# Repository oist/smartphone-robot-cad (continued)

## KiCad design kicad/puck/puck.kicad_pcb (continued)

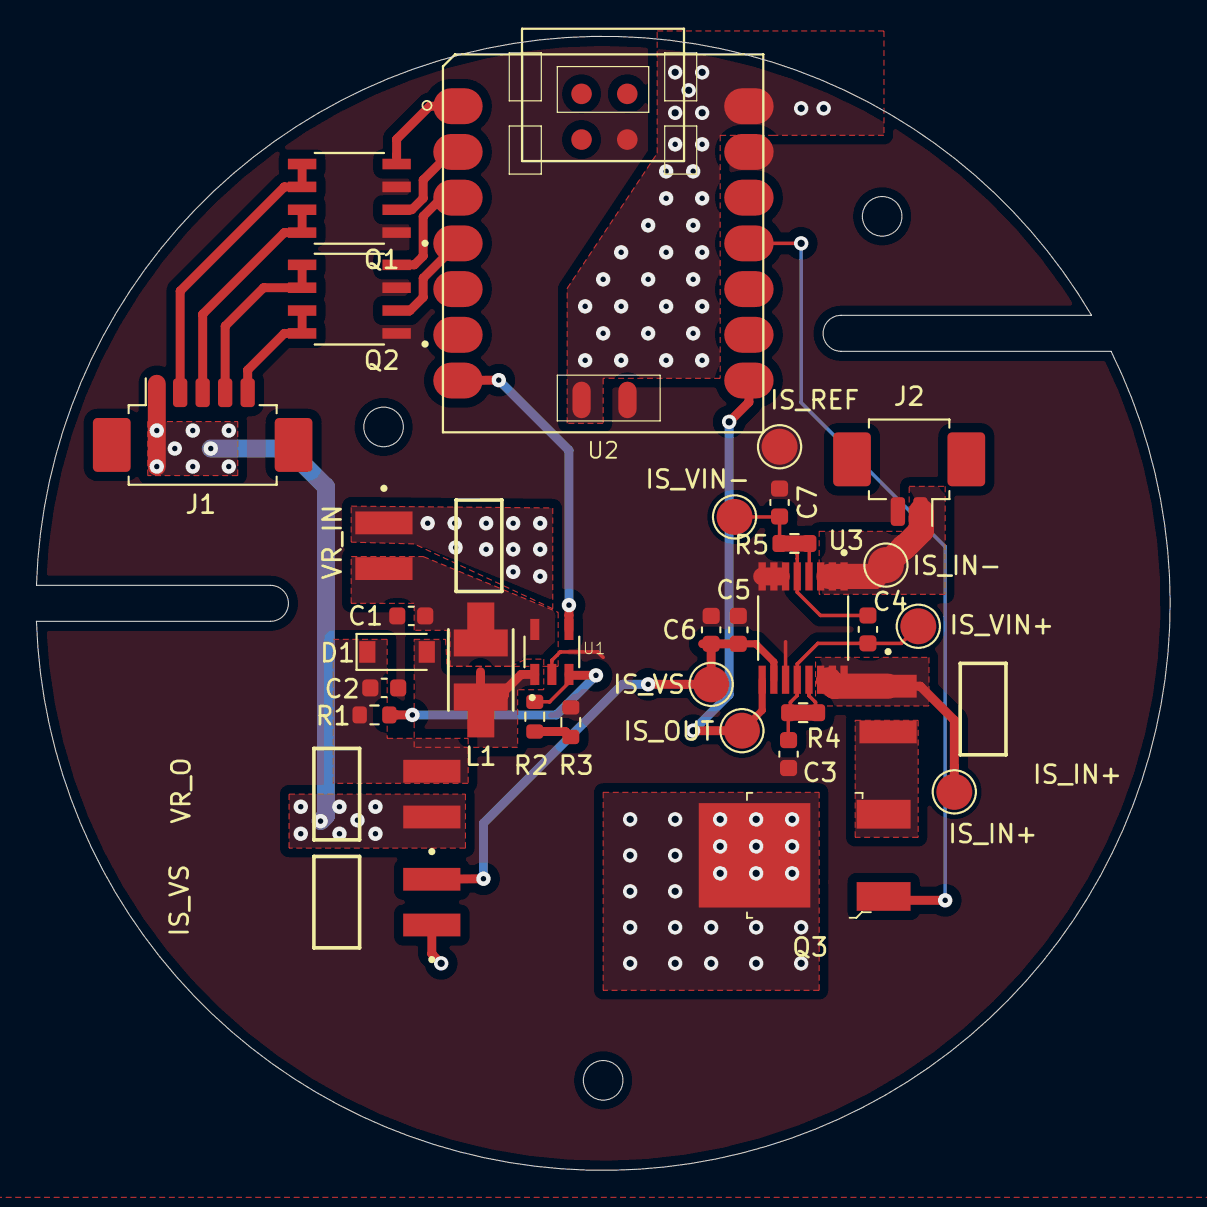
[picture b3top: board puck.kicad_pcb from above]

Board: 2 copper layers, 63.0 x 63.0 mm, 33 parts (0 on the bottom side), 27 nets.

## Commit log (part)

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2023-06-06 Updating working dir for config
2023-06-06 Adding gitignore for config
2023-06-07 Rebased footprints module onto current master
2023-07-19 Adding separable pin headers symbols for longer pin header
2023-07-19 Add button for boot select like on PICO to allow drag/drop programming
2023-07-19 Adding TL3305AF260QG
2023-07-19 Add current breaks between each section of hardware.
2023-07-19 Made R66 DNP
2023-07-19 Added set resistor for LDO and changed size to 0603 for LDO output capacitor as recommended by datasheet Output Capacitor Selection
2023-07-19 custom_transistors:ON_Semiconductor-568AL-10_2013-O-MFG footprint 3d model dot to correct corner
2023-07-19 Updated voltage translation mosfets to lower V_th mosfets
2023-07-19 Adding JST_-_B6B-ZR-SM4-TF
2023-07-19 Hold bufferin rp2040sheet to vio during startup
2023-07-19 Added RC2 voltage translator
2023-07-19 Hide all test point values keep ref
2023-07-19 Adding 7.0 config files
2023-07-25 Removing firmware-specific submodules from pcb branch
2023-07-25 Adding wireless coil jst header
2023-07-26 Updating kicad_common.json to correct directories
2023-07-26 Adding switch to connect d+/- from both USB from Pc to pi
2023-07-26 Adding motor and wheels to custom_connectors.pretty/CONN_B6B-ZR-SM4-TF_JST.kicad_mod
2023-07-26 Flipping battery to other side of board
2023-07-27 Eleminated 5V rail and corrected a few mistakes in SIMO config
2023-07-30 Updating reference after seeing Archive3DModels fail
2023-07-31 Export 3D models to local project
2023-07-31 Fixed floating zone supposed to be GND
2023-07-31 Added removed Package_X1SON:TPD1E05U06DPYR
2023-07-31 updated all footprint fields in schematic symbols with local robot ones
2023-07-31 Exported all schematic symbols to local robot and refer to them in all symbols
2023-07-31 Adding Switch_R_SMD_3pin symbol
2023-07-31 removed i2c switch for external master. Not needed due to not using custom scripts on the Max77958 in favor of mcu control via firmware
2023-07-31 Adding JS202011JCQN to project in place of other switch
2023-07-31 Swapping out SW4_PTS815 SJM 250 SMTR LFS_CNK for prevvious tactile switch on rp2040
2023-07-31 Adding XTAL_ECS-120-8-36-CKM-TR3 in place of previous crystal
2023-08-01 Replaced all test points with SMD parts where possible
2023-08-01 Moving SWCLK and SWD to pin header on rp2040 UART
2023-08-01 finished grouping paired 0ohm resistors
2023-08-01 Adding power flags to side of 0ohm resistors for electrical checks
2023-08-01 Ignoring some warnings about GND naming duplications. Electrical Rules Checker clear.
2023-08-01 Adding THT leads for rocker switch and 2 ohm resistors to implement it if needed
2023-08-02 Adding B12H1UYG-20D000134U1930 LED
2023-08-02 Swapped all LEDS out for board edge ones
2023-08-02 Replacing LEDs with side mounted ones, and added an LED driver for the two that don't have a driver
2023-08-04 Adding robot lib to favorites
2023-08-04 adding SW_SPST symbol to robot lib
2023-08-04 Adding TE_1-1123723-2 to lib
2023-08-04 Exported step file for motor
2023-08-04 Added similar JST connector
2023-08-04 init commit of micromotor
2023-08-04 Added 90mm wheels step and to assembly
2023-08-04 Added 40mm wheels step and to assembly
2023-08-04 Rearanged tree for motor
2023-08-04 Made PCB assembly and added to Robot
2023-08-04 Added initial sketch for body enclosure
2023-08-04 Aligned wheels and motor and phone to get a sense of spacing.
2023-08-04 Adding init blender file
2023-08-05 Adding plug to motor cable 3d model
2023-08-05 Adding pixel3a mount
2023-08-05 Adding prl config file to gitignore
2023-08-05 Adding header models to local as well
2023-08-05 Updated phone mounting sleeve and position
2023-08-05 Locking positions of phone, motors, and battery
2023-08-05 changed colors of pixel3a models
2023-08-06 Moving battery back but with enough space for mounting holes
2023-08-06 wip pixel mount
2023-08-06 wip 3d models
2023-08-07 wip models
2023-08-07 Adding load switch to battery protection circuit
2023-08-07 Moving molex and wheel connectors around
2023-08-07 Adding robot.pretty/MountingHole_2.2mm_M2.kicad_mod
2023-08-07 Increased clearance on mounting holes
2023-08-07 Removing duplicate headers
2023-08-08 Updating battery holder footprint to include gaps in courtyard
2023-08-08 Removing no longer relevant text comment about alternative headers
2023-08-08 changing UART header to 2.54mm header and moving bulk capacitance after load switch.
2023-08-08 reset the offset of qfn
2023-08-08 adding a couple more local 3d packages
2023-08-09 Removing changes to kicad_pro made by Kadir on accident
2023-08-09 Removing a bunch of unneccesary symbol properties
2023-08-09 Adding pin numbers for connector to remove PCB error
2023-08-09 added erc exclusions
2023-08-09 Updating power flag to local symbol
2023-08-10 updating all footprints from lib. Rotated a bunch of pads from 270 to 90 and so forth. Looks like might have come from when flipped all parts to other side of board?
2023-08-10 fixed hovering AP33771DKZ13 model
2023-08-10 Updated battery model offset to match library
2023-08-10 updating global paths to 3d models to project relative ones for usb for phone and motor headers
2023-08-10 placed remaining components
2023-08-10 Adding back in exclusions
2023-08-10 Thinned out silkscreen lines so not on top of pad for USB4120-03-C_REVA
2023-08-11 Updated errors in SN74AHC125RGYR footprint including non-mask defined pads
2023-08-11 Added GND vias to isolated zone and removed all zones < 20mm^2
2023-08-11 Adding courtyard to TVS0500DRVR
2023-08-11 moved tp32 above tp31
2023-08-11 fixed c37-c17 gnd connection error
2023-08-11 move tp21 to more accessible place
2023-08-11 Rotated a few smd test points and moved LEDs closer to board edge
2023-08-11 adding a bunch of thermal reliefs
2023-08-11 Adding a few more warnings for DRC
2023-08-11 Removing some unknown pcb properties
2023-08-11 Updating courtyard on battery. 3d model profile was wrong
2023-08-13 Added all netties and net classes for 3A traces to schematic and updated PCB, but haven' t routed anything yet
2023-08-13 Adding all power_1A net classes and net ties
2023-08-13 Updating symbol fields for BOM completion.
2023-08-13 fixing a few more BOM related issues
2023-08-14 placed netties
2023-08-14 increased trace width btw R73-J4
2023-08-14 fixing Charger.kicad_sch net tie needs on STAT LED and EXTSM also needed to be a signal trace
2023-08-14 Changed 2A net tie to 0.3mm trace tie
2023-08-14 Updating netties to not include polygon
2023-08-14 Changed TP from 5004 to emtpy THT for potential switch later.
2023-08-14 fixed drc errors for TP12
2023-08-14 DRC fixes for R42 net tie errors
2023-08-14 fixing DRC errors associated with SYS in for USB-PD-PhonePC sheet
2023-08-14 fixing net tie issue with VBUS_Phone_PS and nearby nets
2023-08-14 fixing poorly routed GPIO5 on max77958
2023-08-15 Ignoring one more DNP cap warning
2023-08-15 Removed some unconnected tracks
2023-08-15 Fixed scope in rules for inner layers
2023-08-15 Removing old netclass patterns
2023-08-15 Added custom rules to exclude BGA/WLP trace thickness check
2023-08-15 Updating rules to include U16 and U17 for thin traces
2023-08-15 moved test points into battery holder courtyard
2023-08-15 BOM exclusions for net ties and n/a part test points
2023-08-15 BOM value fixes
2023-08-15 Adding robot to pinned symbol libs
2023-08-15 Updating bom.py and robot.xml
2023-08-15 fixed up zone on OUT_P1
2023-08-15 fixed up batt zone
2023-08-15 Updating wireless charger to 3A net class and added zone
2023-08-16 fixing a few more zone related DRC errors
2023-08-16 Adding two more net labels to diff pair signals
2023-08-17 reviewed and made small changes usb data lines
2023-08-17 Adding C_1206_3216Metric_AlPoly_Combo
2023-08-17 Updating footprint for IC_DRV8830DRCR to include vias
2023-08-18 Adding optimal track width for 2A net class
2023-08-18 Major revision moving motor drivers closer to motor headers
2023-08-18 Fixing some more minor DRC errors
2023-08-18 Removing islands from GND zone
2023-08-18 Resolving all DRC and ERC errors/warnings
2023-08-18 Added wireless recevier separate from header
2023-08-18 Adding external switch to BOM
2023-08-18 Adding wheels to sch for BOM
2023-08-18 gerbers submitted to NextPCB
2023-08-21 Updating reference to 1206 cap 3d package to relative path
2023-08-21 Placing origin
2023-08-21 Updating part number for 0805 100uF caps
2023-08-21 updaintg bom.py to include stock for DNP parts
2023-08-22 Adding STWLC38JRM to libs
2023-08-23 wireless receiver schematic finished (other than BOM)
2023-08-23 Updating all wireless passives to required part numbers. Still missing less restrictive ones
2023-08-23 Updating PCB with new footprints
2023-08-23 Updated 100uF caps to 1206 footprint to allow for 6.3V ratings
2023-08-23 First attempt to organize wireless caps
2023-08-23 Updating RMCF0603FT649K to RC0402FR-07649KL
2023-08-23 Adding passive footprint bom generator
2023-08-25 fixed two wrong product foorprint mismatches
2023-08-25 Updating tht mounting holes for coil as not in BOM
2023-08-25 Updated power path from VBus_Ext to top and bottom layers and thicker zone.
2023-08-25 Updating production files
2023-08-28 Updating part number to MAX77857BEWB+
2023-08-28 Updating bom with updated part numbers and stock qty
2023-09-05 updating DRV8830DRCR footprint
2023-09-05 Replacing wrong part number for USB4151-GF-C
2023-09-05 Updating fab files after changes requested from NextPCB
2023-09-13 Adding overlap on nettie footprint as per NextPCB request
2023-09-15 Initial robot body design sent to Ken-san
2023-09-28 Increased size of vias under USB
2023-09-28 Updating gerbers
2023-09-28 Adding type field to all parts for pcbway
2023-09-29 Updated via-in-pad requirements
2023-10-02 Updating gerbers based on 16 quotes
2023-10-03 Moving copper 0.21mm from edge cuts as per recommendation
2023-10-05 Updating full partnumber for powermux
2023-10-05 Replacing YJL3416A with AS2312
2023-10-05 Changing mask to green since jlcpcb charged 0 less for it
2023-10-23 Updating led footprints to indicate diode orientation
2023-10-25 Changing kicad_common.json to gitSSD dir
2023-10-25 Hiding DNP R10 3d model
2023-10-25 Hiding DNP R80 3d model
2023-10-25 Hiding DNP R91 3d model
2023-10-25 Updating paths to 3d models for C109 and C127
2023-10-25 Hiding DNP models for C74, C89, C86, C90
2023-10-25 Hiding DNP models for R13
2023-10-25 Made visible 3d model for C125
2023-11-20 deeper cavity for the pins, and a larger space for the wireless coil
2023-11-22 Updating top cover to include hole for button
2024-01-17 Adding button_hole test and parts
2024-01-31 Adding tests for counter_sunk holes
2024-02-05 Updating size of shaft adapter after initial batch print failed
2024-05-14 Importing 3d cad media from meta project repo
2024-07-10 Removing outdated Tina electrical cad designs
2024-07-10 Removing outdated pspice files
2024-07-10 Removed all outdated files and renamed some to be more descriptive
2024-07-11 Removed a duplicate cad file
2024-07-15 changing dir names for body and pcb
2024-07-23 Reduced width to minimum. Uncertain whether this will print or be secure with screw hole ideas used.
2024-07-23 decreasing all dimensions as much as possible, adding cut to bottom sharp corners, increased spacing in motor mount gap from 1 to 1.5mm, fasteners adjusted for thin body
2024-07-24 Added tail ball
2024-07-25 Adding urdf generation via https://github.com/galou/freecad.cross
2024-07-25 Adding gitignore for *.FCBak
2024-07-25 Added missing hole for switch
2024-07-29 Adding switch mount fix part to model
2024-08-08 Adding LED explanation to readme
2024-08-30 Adding new body to exploded view
2025-04-10 Storing svg diffs between working and broken boards for future reference
2025-05-28 WIP Total rework of model from ground up
2025-06-12 Hardware connection holes, feet/tail, and bottom firmware flash holes
2025-06-12 Adding print files
2025-09-22 Adding pixel3A phone holder body
2025-09-30 Separated out printing assembly
    Adding screw hole to tail
    Adding battery indent cutout to top part
2025-10-05 Replacing extra bottom holes with those under feet. Removing top tail hole and using through hole on bottom. Updated fasteners
2025-10-07 Fixing switch cutout cutout length.
